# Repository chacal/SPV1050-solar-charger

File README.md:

# SPV1050 Solar Charger
KiCad hardware files for [STMicroelectronics SPV1050](https://www.st.com/en/power-management/spv1050.html) based solar charger PCB.

## Schematics

* [PDF](SPV1050%20solar%20charger%20v2.pdf)

## Board rendering

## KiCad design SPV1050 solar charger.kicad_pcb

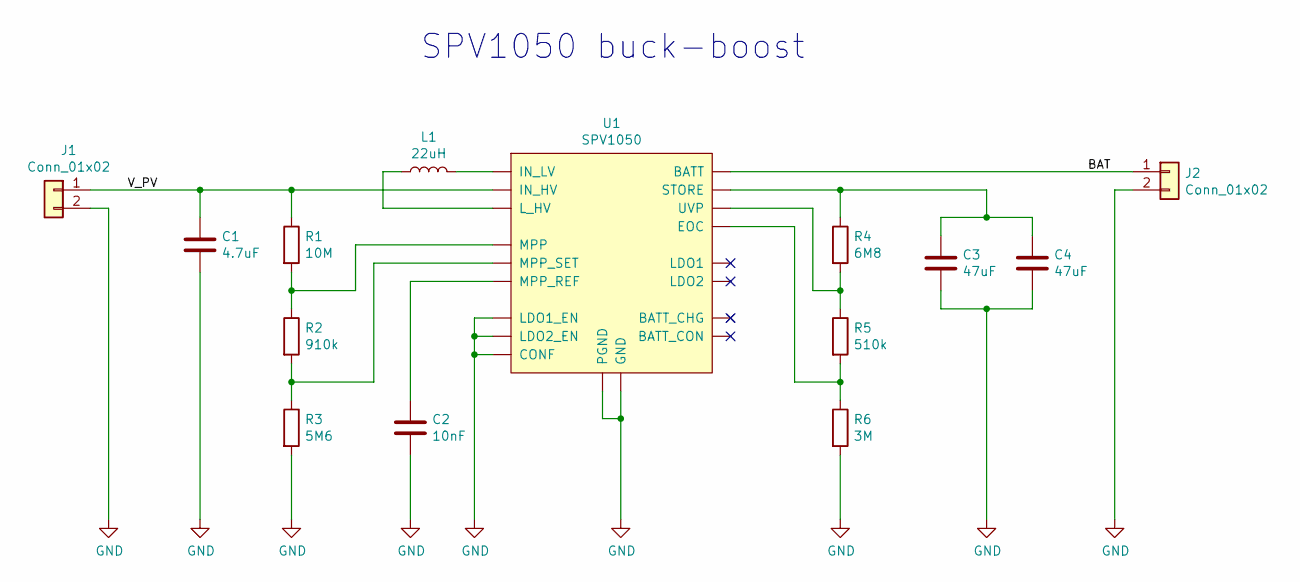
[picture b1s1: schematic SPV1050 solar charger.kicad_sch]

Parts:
C1: 4.7uF; C_0805_2012Metric
C2: 10nF; C_0805_2012Metric
C3, C4: 47uF; C_0805_2012Metric
J1, J2: Conn_01x02; JST_PH_S2B-PH-K_1x02_P2.00mm_Horizontal
L1: 22uH; CD43
R1: 10M; R_0805_2012Metric
R2: 910k; R_0805_2012Metric
R3: 5M6; R_0805_2012Metric
R4: 6M8; R_0805_2012Metric
R5: 510k; R_0805_2012Metric
R6: 3M; R_0805_2012Metric
U1: SPV1050; UQFN-20-1EP_3x3mm_P0.4mm_EP1.85x1.85mm_handsolder

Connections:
/BAT: J2.1, U1.14 (BATT)
/V_PV: C1.1, J1.1, R1.1, U1.20 (IN_HV)
GND: C1.2, C2.2, C3.2, C4.2, J1.2, J2.2, R3.2, R6.2, U1.4 (GND), U1.5 (LDO1_EN), U1.6 (LDO2_EN), U1.13 (CONF), U1.17, U1.18 (PGND), U1.21
unnamed: C2.1, U1.3 (MPP_REF)
unnamed: C3.1, C4.1, R4.1, U1.15 (STORE)
unnamed: L1.1, U1.19 (L_HV)
unnamed: L1.2, U1.16 (IN_LV)
unnamed: R1.2, R2.1, U1.1 (MPP)
unnamed: R2.2, R3.1, U1.2 (MPP_SET)
unnamed: R4.2, R5.1, U1.10 (UVP)
unnamed: R5.2, R6.1, U1.9 (EOC)

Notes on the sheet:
SPV1050 buck-boost

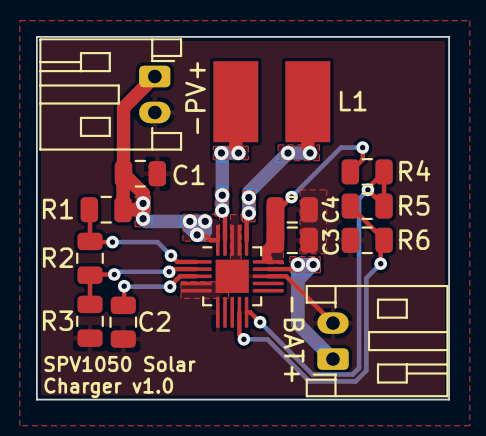
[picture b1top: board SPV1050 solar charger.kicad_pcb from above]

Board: 2 copper layers, 22.9 x 20.1 mm, 14 parts (0 on the bottom side), 11 nets.

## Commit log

2022-01-21 Add schematics as PDF
2022-01-21 Add rev 1.0
2022-01-21 Add 3D rendering of rev 2.0 board
2022-01-21 Add revision 2.0
    Fine tuned PCB layout
